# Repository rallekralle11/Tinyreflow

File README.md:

# Tinyreflow
Inspired by afterearthLTD's reflow plate, but using fewer and simpler, THT components.

Everything is functional but the code only has a curve set up for low-temp solder so far.

Licensed under CERN-OHL-P

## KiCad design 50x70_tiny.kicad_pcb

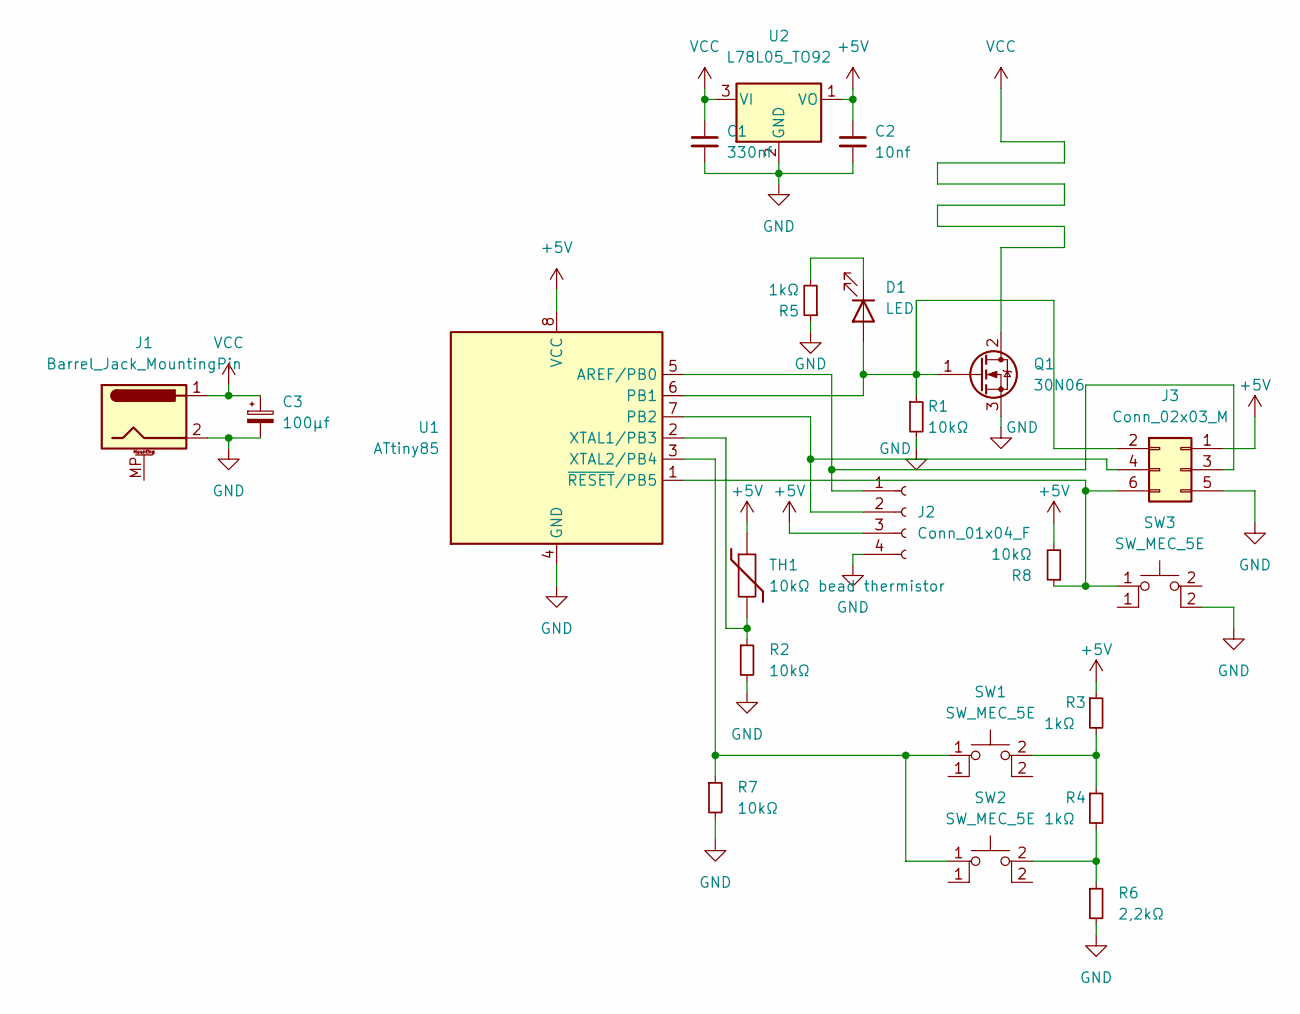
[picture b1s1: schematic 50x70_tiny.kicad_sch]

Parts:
C1: 330nf; C_Disc_D5.0mm_W2.5mm_P2.50mm
C2: 10nf; C_Disc_D5.0mm_W2.5mm_P2.50mm
C3: 100µf; CP_Radial_D6.3mm_P2.50mm
D1: LED; LED_D3.0mm
J1: Barrel_Jack_MountingPin; BarrelJack_Horizontal
J2: Conn_01x04_F; PinSocket_1x04_P2.54mm_Vertical
J3: Conn_02x03_M; PinHeader_2x03_P2.54mm_Vertical
Q1: 30N06; TO-220F-3_Vertical
R1, R2, R7, R8: 10kΩ; R_Axial_DIN0207_L6.3mm_D2.5mm_P7.62mm_Horizontal
R3, R4, R5: 1kΩ; R_Axial_DIN0207_L6.3mm_D2.5mm_P7.62mm_Horizontal
R6: 2,2kΩ; R_Axial_DIN0207_L6.3mm_D2.5mm_P7.62mm_Horizontal
SW1, SW2, SW3: SW_MEC_5E; SW_PUSH_6mm_H4.3mm
TH1: 10kΩ bead thermistor; R_Axial_DIN0204_L3.6mm_D1.6mm_P2.54mm_Vertical
U1: ATtiny85; DIP-8_W7.62mm
U2: L78L05_TO92; TO-92_Wide

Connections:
+5V: C2.1, J2.3, J3.1, R3.1, R8.2, TH1.1, U1.8 (VCC), U2.1 (VO)
GND: C1.2, C2.2, C3.2, J1.2, J2.4, J3.5, Q1.3 (S), R1.2, R2.2, R5.1, R6.2, R7.2, SW3.2, U1.4 (GND), U2.2 (GND)
unnamed: D1.1 (K), R5.2
unnamed: D1.2 (A), J3.2, Q1.1 (G), R1.1, U1.6 (PB1)
unnamed: J2.1, J3.3, U1.5 (AREF/PB0)
unnamed: J2.2, J3.4, U1.7 (PB2)
unnamed: J3.6, R8.1, SW3.1, U1.1 (~RESET/PB5)
unnamed: R2.1, TH1.2, U1.2 (XTAL1/PB3)
unnamed: R3.2, R4.1, SW1.2
unnamed: R4.2, R6.1, SW2.2
unnamed: R7.1, SW1.1, SW2.1, U1.3 (XTAL2/PB4)
VCC: C1.1, C3.1, J1.1, Q1.2 (D), U2.3 (VI)

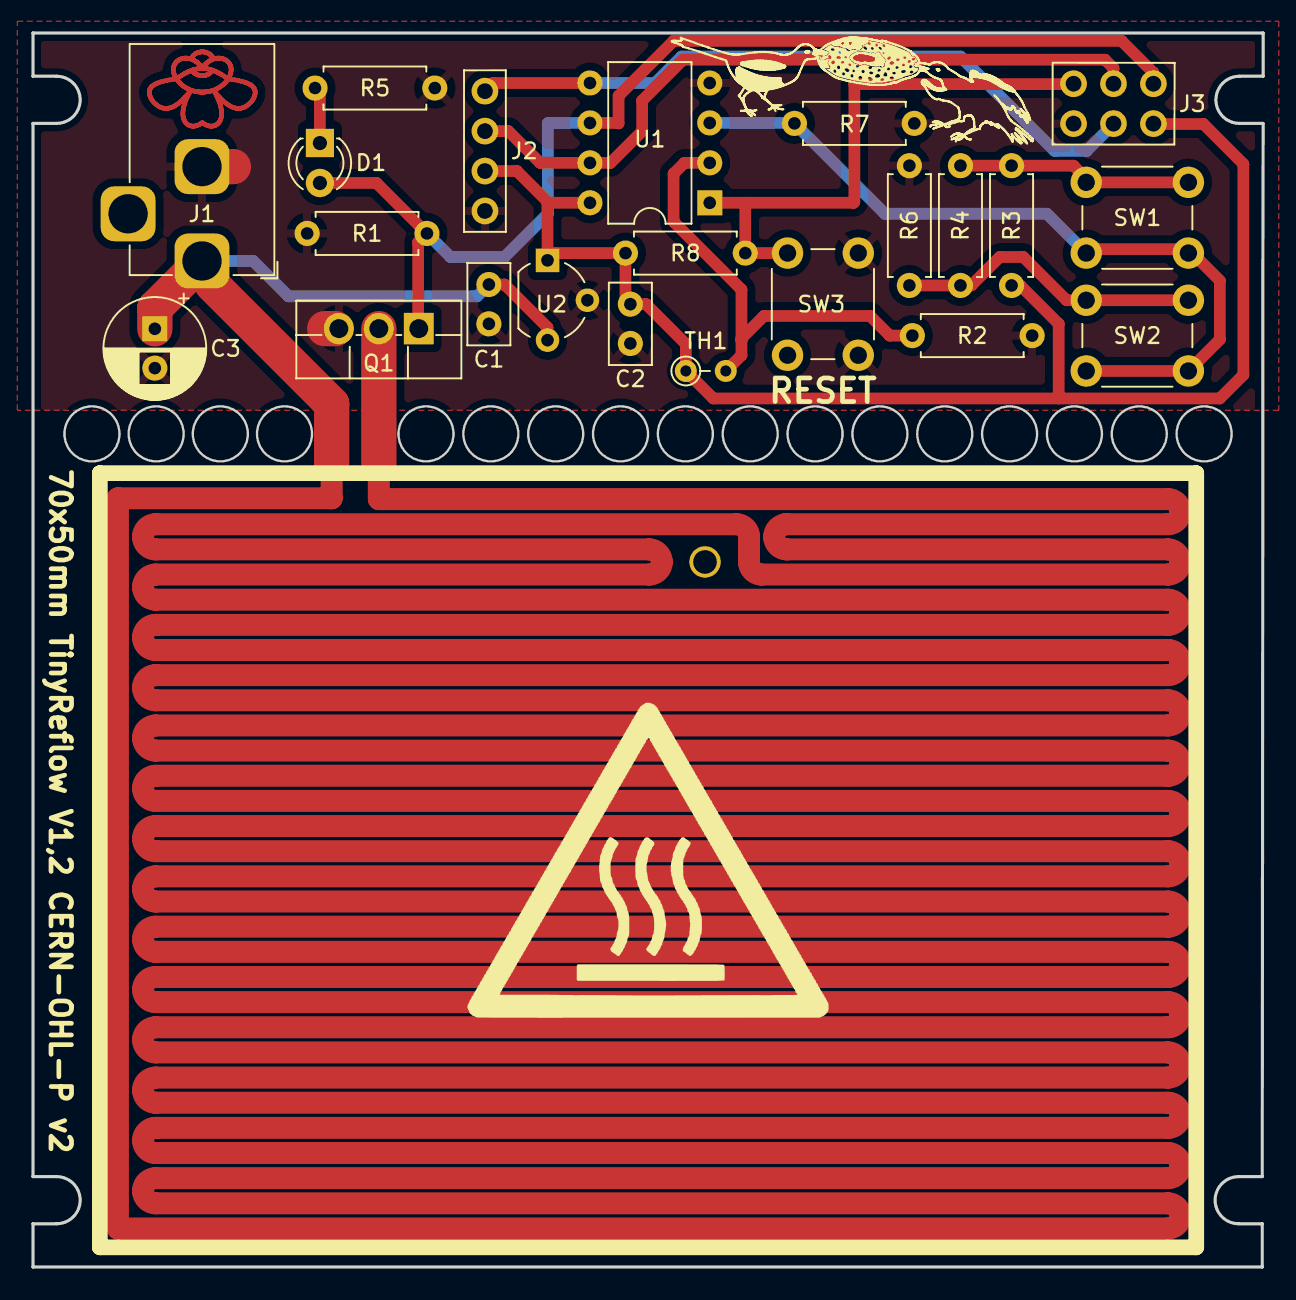
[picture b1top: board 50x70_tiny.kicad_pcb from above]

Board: 2 copper layers, 78.2 x 78.5 mm, 22 parts (0 on the bottom side), 12 nets.

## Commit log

2022-10-29 initial
2022-10-29 readme
2022-11-08 redesign, 3D models and a picture
2022-11-08 gerber and stuff
2022-11-11 bad picture change
2022-11-15 second version code nearly finished and functional. only for low temp bismuth solder so far
2022-11-26 lil update
2022-11-26 bom+
2023-01-06 forgot

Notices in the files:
50x70_tiny.kicad_pcb:
70x50mm TinyReflow V1,2 CERN-OHL-P v2
